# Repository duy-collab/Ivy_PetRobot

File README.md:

# Ivy_PetRobot

Ivy_PetRobot is an interactive AI-powered pet robot designed to engage with users through voice, facial recognition, and dynamic behaviors. It brings personality to robotics with a focus on emotional expression and smart interaction.

## Features

- 🎤 Voice recognition using Whisper
- 🗣️ Speech synthesis with natural voice
- 🧠 AI-powered conversation using OpenAI API
- 📷 Image recognition and scene description
- 😺 Facial emotion display via LCD and LED
- 🛞 Motor control for mobility and animation
- 🕹️ ESP32 & Raspberry Pi integration
- 📡 MQTT cloud communication with HiveMQ
- 📁 I2C communication for command synchronization

## Technologies Used

- Raspberry Pi OS Bullseye
- ESP32 microcontroller
- INMP441 microphone (I2S)
- MAX98357A speaker amp (I2S)
- ILI9341 / ST7796 LCD with GT911 touch
- OpenAI Whisper and GPT APIs
- HiveMQ MQTT for IoT data streaming
- Python, C++ (Arduino), Bash

## Repository Structure

/Ivy_PetRobot
├── raspberry_pi/ # Main AI logic, image processing, audio I/O

├── esp32/ # Display, motors, expression handling

├── arduino_nano/ # Optional: audio capture and I2C transmission

├── assets/ # Face expression images, sound files

├── docs/ # Reports and design documentation

└── README.md

## Credits

Final year thesis project by Luong Ho Khanh Duy, Student ID 2113013 and Tran Kim Khanh, Student ID 2113717 — Department of Electrical Engineering, Ho Chi Minh City University of Technology (HCMUT).

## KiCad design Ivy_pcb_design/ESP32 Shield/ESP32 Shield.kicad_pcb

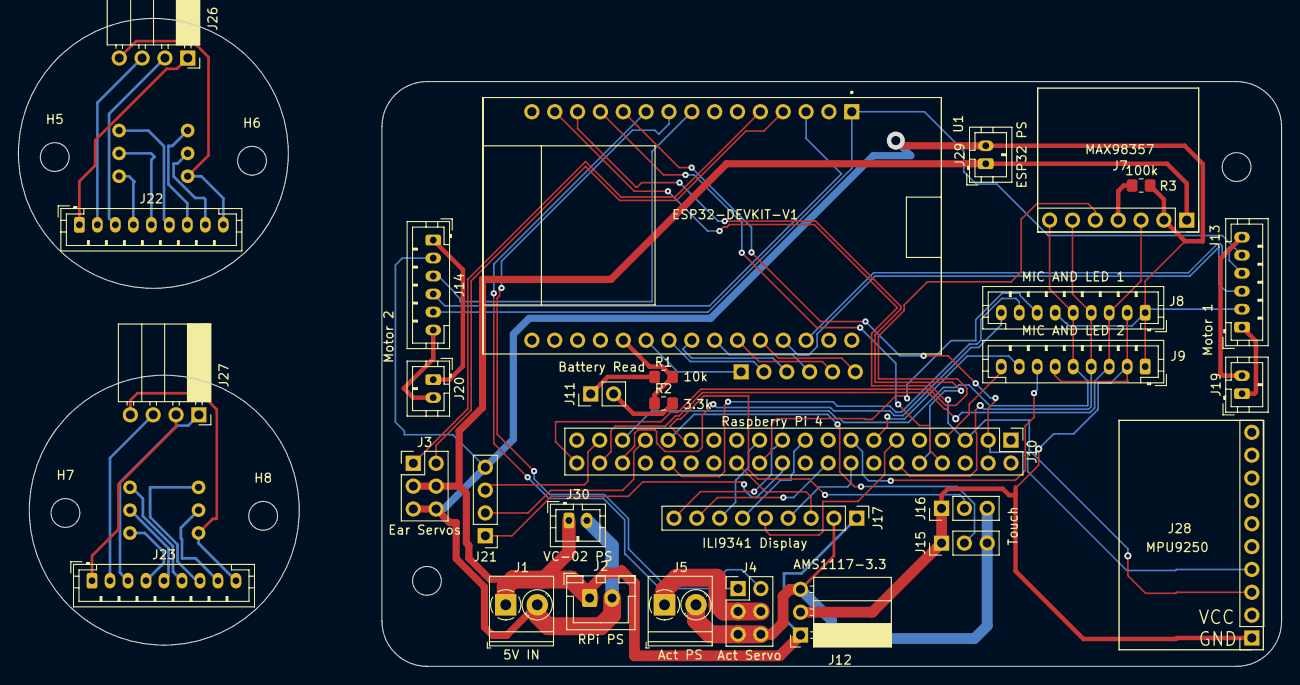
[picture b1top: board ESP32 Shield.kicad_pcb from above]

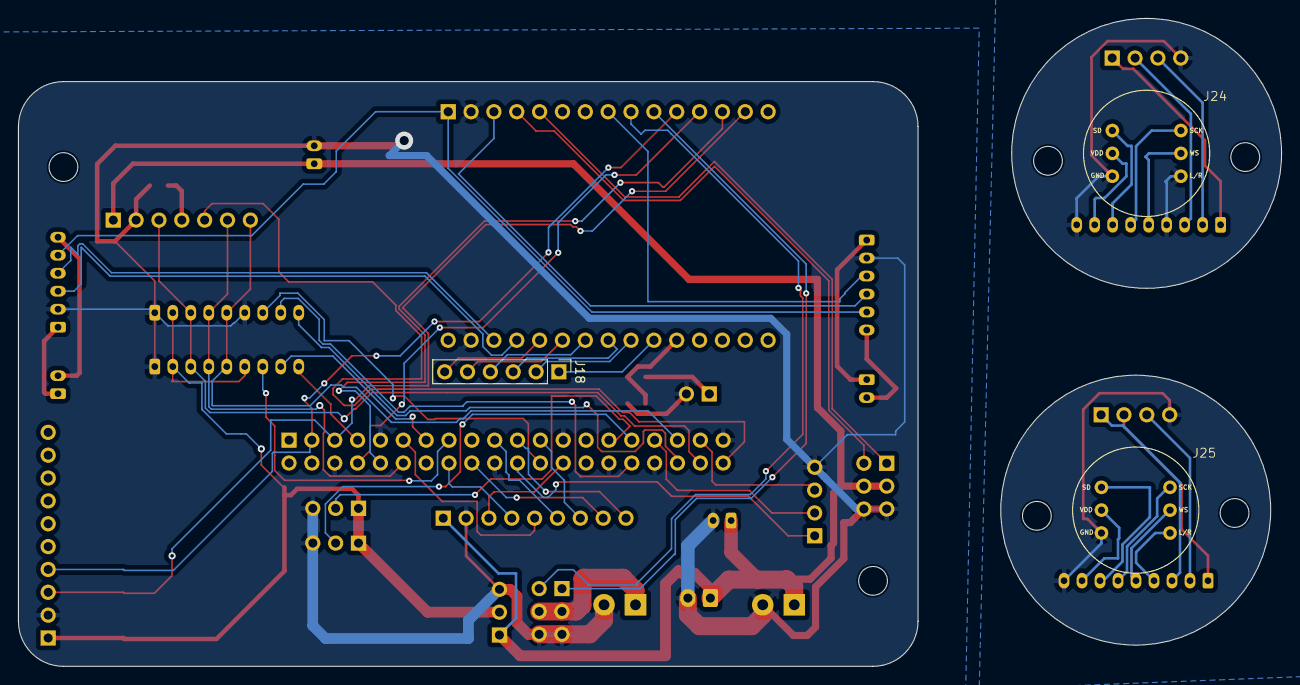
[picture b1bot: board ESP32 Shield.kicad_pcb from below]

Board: 2 copper layers, 140.4 x 72.0 mm, 39 parts (3 on the bottom side), 65 nets.

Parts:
H2, H3, H5, H6, H7, H8: MountingHole; MountingHole_3.2mm_M3
J1: 5V IN; TerminalBlock_Phoenix_PT-1,5-2-3.5-H_1x02_P3.50mm_Horizontal
J2: RPi PS; JST_XH_B2B-XH-A_1x02_P2.50mm_Vertical
J3: Ear Servos; PinHeader_2x03_P2.54mm_Vertical
J4: Act Servo; PinHeader_2x03_P2.54mm_Vertical
J5: Act PS; TerminalBlock_Phoenix_PT-1,5-2-3.5-H_1x02_P3.50mm_Horizontal
J7: MAX98357; PinSocket_1x07_P2.54mm_Vertical
J8: MIC AND LED 1; JST_PH_B9B-PH-K_1x09_P2.00mm_Vertical
J9: MIC AND LED 2; JST_PH_B9B-PH-K_1x09_P2.00mm_Vertical
J10: Raspberry Pi 4; PinHeader_2x20_P2.54mm_Vertical
J11: Battery Read; PinHeader_1x02_P2.54mm_Vertical
J12: AMS1117-3.3; PinSocket_1x03_P2.54mm_Horizontal
J13: Motor 1; JST_PH_B6B-PH-K_1x06_P2.00mm_Vertical
J14: Motor 2; JST_PH_B6B-PH-K_1x06_P2.00mm_Vertical
J15: Touch; PinHeader_1x03_P2.54mm_Vertical
J16: Touch 3; PinHeader_1x03_P2.54mm_Vertical
J17: ILI9341 Display; PinHeader_1x09_P2.54mm_Vertical
J18: L298N; PinHeader_1x06_P2.54mm_Vertical
J19: L298N-Motor 1; JST_PH_B2B-PH-K_1x02_P2.00mm_Vertical
J20: L298N-Motor 2; JST_PH_B2B-PH-K_1x02_P2.00mm_Vertical
J21: VC-02; PinHeader_1x04_P2.54mm_Vertical
J22: MIC AND LED 1 - EAR; JST_PH_B9B-PH-K_1x09_P2.00mm_Vertical
J23: MIC AND LED 2 - EAR; JST_PH_B9B-PH-K_1x09_P2.00mm_Vertical
J24: MIC 1; INMP441
J25: MIC 2; INMP441
J26: LED 1; PinSocket_1x04_P2.54mm_Horizontal
J27: LED 2; PinSocket_1x04_P2.54mm_Horizontal
J28: MPU9250; PinSocket_1x10_P2.54mm_Vertical
J29: ESP32 PS; JST_PH_B2B-PH-K_1x02_P2.00mm_Vertical
J30: VC-02 PS; JST_PH_B2B-PH-K_1x02_P2.00mm_Vertical
R1: 10k; R_0805_2012Metric_Pad1.20x1.40mm_HandSolder
R2: 3.3k; R_0805_2012Metric_Pad1.20x1.40mm_HandSolder
R3: 100k; R_0805_2012Metric_Pad1.20x1.40mm_HandSolder
U1: ESP32-DEVKIT-V1; MODULE_ESP32_DEVKIT_V1

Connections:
+3.3V: J13.5, J14.5, U1.1 (3V3)
+3.3VA: J8.2, J9.2, J9.6, J12.2, J15.1, J16.1, J28.1
+3.3VRP: J10.1, J10.17
+3.3V_EAR: J22.8, J23.4, J23.8, J24.2, J25.2, J25.6
+5V: J1.1, J2.1, J3.3, J3.4, J7.1, J12.1, J17.1, J29.1, J30.1
+5VRP: J10.2, J10.4
+7.5V: J4.3, J4.4, J5.1
+12V: J11.1, R1.1
/BCLK: J7.6, J8.4, J9.4, J10.12
/BLUE1: J8.9, J10.36
/BLUE1_EAR: J22.1, J26.1
/BLUE2: J9.7, J10.15
/BLUE2_EAR: J23.3, J27.1
/Battery ADC: R1.2, R2.1, U1.20 (D35)
/CS: J10.26, J17.3
/DC/RS: J10.11, J17.5
/DIN: J7.5, J10.40
/ENA: J18.1, U1.21 (D32)
/ENB: J18.6, U1.26 (D14)
/GAIN: J7.4, R3.1
/GPIO2: J10.3, J28.4, U1.11 (D21)
/GPIO3: J10.5, J28.3, U1.14 (D22)
/GPIO4: J9.9, J10.7
/GPIO5: J10.29, J16.2
/GPIO6: J10.31, J15.2
/GPIO8: J8.7, J10.24
/GPIO9: J10.21, J17.9
/GPIO10: J10.19, J17.6
/GPIO11: J10.23, J17.7
/GPIO12: J8.8, J10.32
/GPIO13: J10.33, J21.2
/GPIO14: J10.8, U1.12 (RX0)
/GPIO15: J10.10, U1.13 (TX0)
/GPIO19: J7.7, J8.5, J9.5, J10.35
/GPIO20: J7.3, J8.3, J9.3, J10.38
/GPIO23: J10.16, J17.4
/GPIO24: J10.18, J17.8
/GPIO25: J10.22, J21.1
/GPIO26: J10.37, J21.3
/GPIO27: J9.8, J10.13
/GREEN1_EAR: J22.2, J26.3
/GREEN2_EAR: J23.2, J27.3
/IN1: J18.2, U1.22 (D33)
/IN2: J18.3, U1.23 (D25)
/IN3: J18.4, U1.24 (D26)
/IN4: J18.5, U1.25 (D27)
/Motor 1 (C1): J13.3, U1.27 (D12)
/Motor 1 (C2): J13.4, U1.28 (D13)
/Motor 1 (M1): J13.1, J19.1
/Motor 1 (M2): J13.6, J19.2
/Motor 2 (C1): J14.3, U1.8 (D5)
/Motor 2 (C2): J14.4, U1.3 (D15)
/Motor 2 (M1): J14.1, J20.1
/Motor 2 (M2): J14.6, J20.2
/RED1_EAR: J22.3, J26.2
/RED2_EAR: J23.1, J27.2
/SCK_EAR: J22.6, J23.6, J24.4, J25.4
/SD_EAR: J22.7, J23.7, J24.1, J25.1
/SIG_1: J3.2, U1.4 (D2)
/SIG_2: J3.1, U1.5 (D4)
/SIG_3: J4.2, U1.9 (D18)
/SIG_4: J4.1, U1.10 (D19)
/WS_EAR: J22.5, J23.5, J24.5, J25.5
GND: J1.2, J2.2, J3.5, J3.6, J4.5, J4.6, J5.2, J7.2, J8.1, J8.6, J9.1, J10.6, J10.9, J10.14, J10.20, J10.25, J10.30, J10.34, J10.39, J11.2, J12.3, J13.2, J14.2, J15.3, J16.3, J17.2, J21.4, J28.2, J29.2, J30.2, R2.2, R3.2, U1.2 (GND), U1.29 (GND)
GND_EAR: J22.4, J22.9, J23.9, J24.3, J24.6, J25.3, J26.4, J27.4

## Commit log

2025-05-10 add all files
